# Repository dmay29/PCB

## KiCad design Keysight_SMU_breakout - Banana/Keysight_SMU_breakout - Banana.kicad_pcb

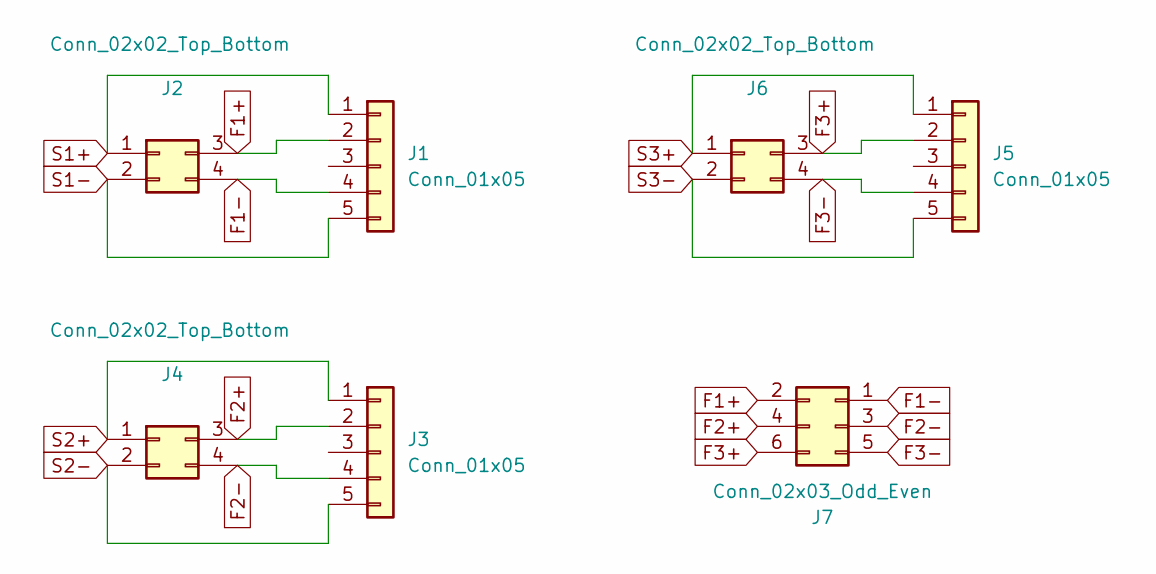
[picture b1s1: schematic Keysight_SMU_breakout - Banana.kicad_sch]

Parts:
J1, J3, J5: Conn_01x05; TerminalBlock_Phoenix_MKDS-1-5-3.81_1x05_P3.81mm_Horizontal
J2, J4, J6: Conn_02x02_Top_Bottom; Quad Banana
J7: Conn_02x03_Odd_Even; PinHeader_2x03_P2.54mm_Vertical

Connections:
F1+: J1.2, J2.3, J7.2
F1-: J1.4, J2.4, J7.1
F2+: J3.2, J4.3, J7.4
F2-: J3.4, J4.4, J7.3
F3+: J5.2, J6.3, J7.6
F3-: J5.4, J6.4, J7.5
S1+: J1.1, J2.1
S1-: J1.5, J2.2
S2+: J3.1, J4.1
S2-: J3.5, J4.2
S3+: J5.1, J6.1
S3-: J5.5, J6.2

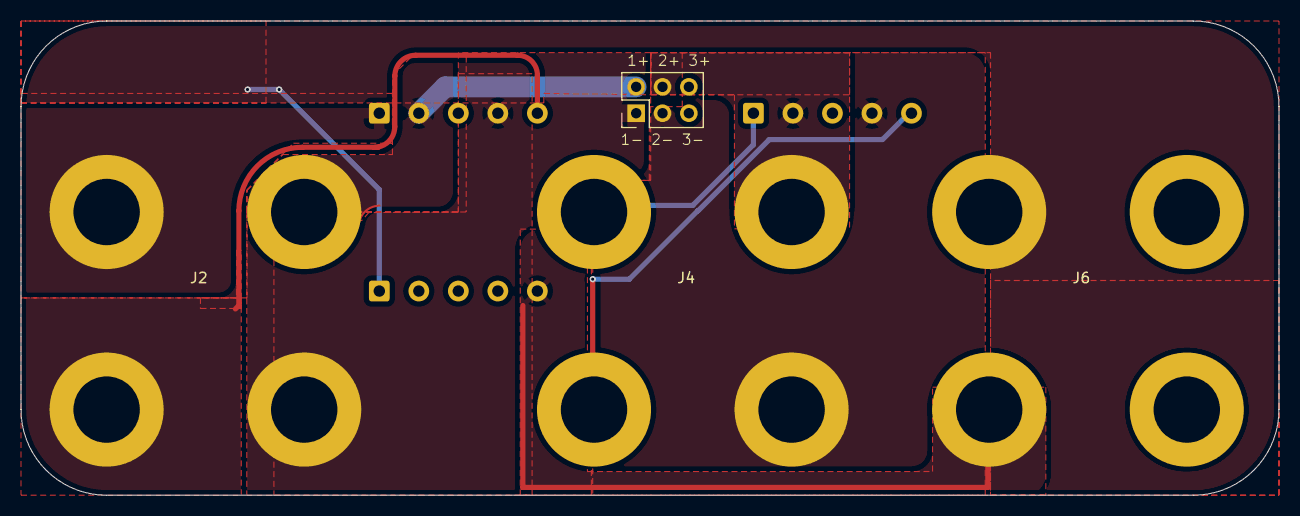
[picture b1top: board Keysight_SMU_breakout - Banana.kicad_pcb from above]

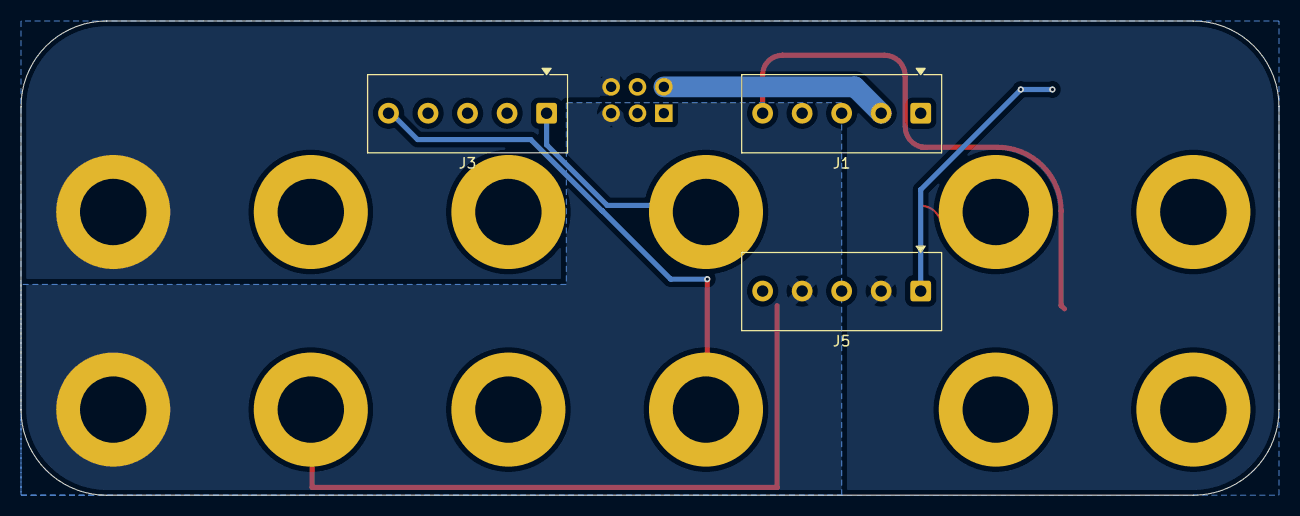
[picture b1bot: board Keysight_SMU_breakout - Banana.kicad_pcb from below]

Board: 2 copper layers, 121.3 x 45.7 mm, 7 parts (3 on the bottom side), 12 nets.

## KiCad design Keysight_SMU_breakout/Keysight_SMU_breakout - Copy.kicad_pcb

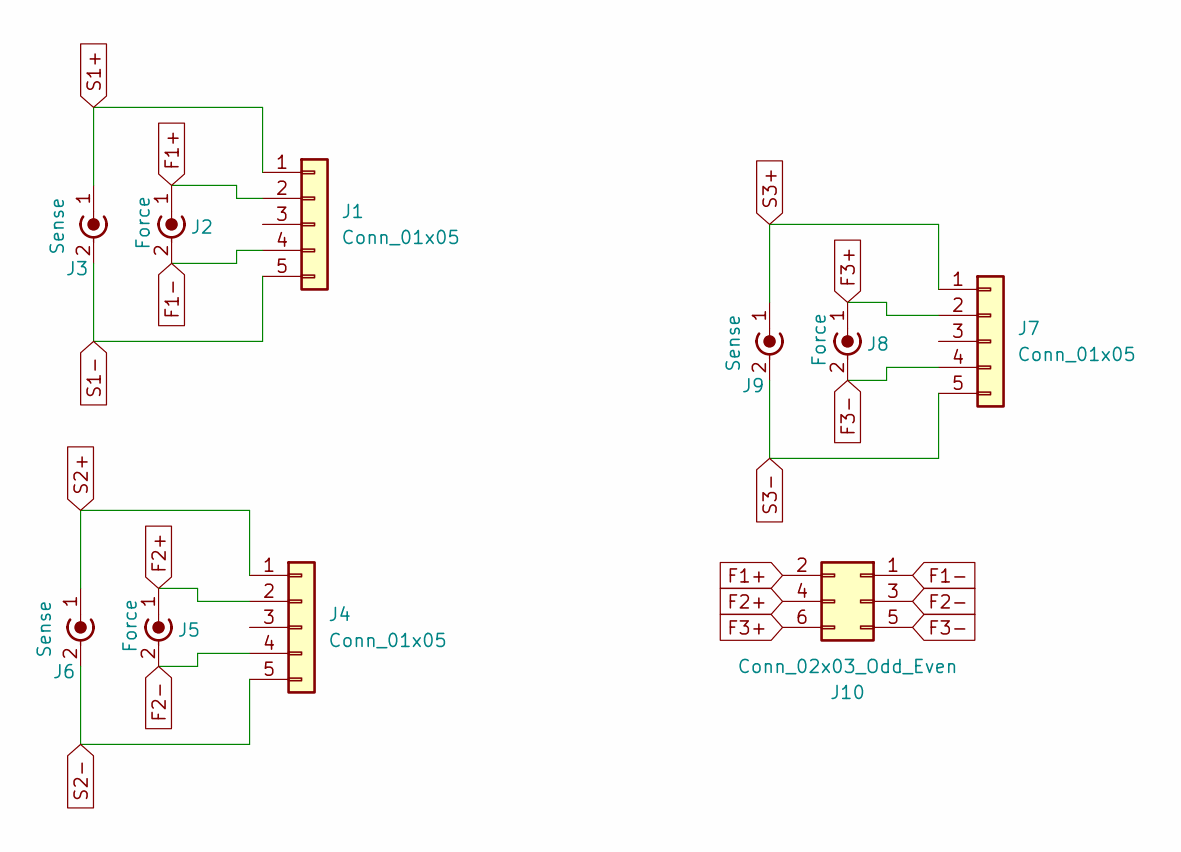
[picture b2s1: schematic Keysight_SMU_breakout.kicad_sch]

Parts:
J1, J4, J7: Conn_01x05; TerminalBlock_Phoenix_MKDS-1-5-3.81_1x05_P3.81mm_Horizontal
J2, J5, J8: Force; BNC_TEConnectivity_1478204_Vertical
J3, J6, J9: Sense; BNC_TEConnectivity_1478204_Vertical
J10: Conn_02x03_Odd_Even; PinHeader_2x03_P2.54mm_Vertical

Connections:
unnamed: J1.1, J3.1 (In)
unnamed: J1.2, J2.1 (In), J10.2
unnamed: J1.4, J2.2 (Ext), J10.1
unnamed: J1.5, J3.2 (Ext)
unnamed: J4.1, J6.1 (In)
unnamed: J4.2, J5.1 (In), J10.4
unnamed: J4.4, J5.2 (Ext), J10.3
unnamed: J4.5, J6.2 (Ext)
unnamed: J7.1, J9.1 (In)
unnamed: J7.2, J8.1 (In), J10.6
unnamed: J7.4, J8.2 (Ext), J10.5
unnamed: J7.5, J9.2 (Ext)

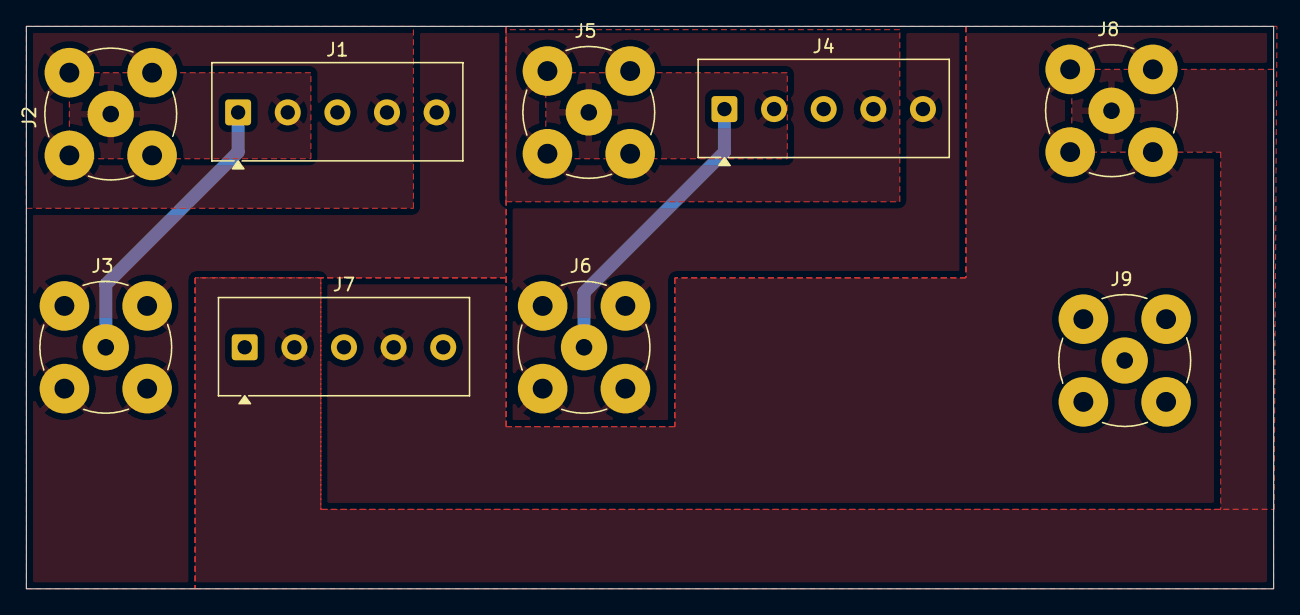
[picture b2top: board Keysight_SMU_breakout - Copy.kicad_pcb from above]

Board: 2 copper layers, 95.8 x 43.2 mm, 9 parts (0 on the bottom side), 12 nets.

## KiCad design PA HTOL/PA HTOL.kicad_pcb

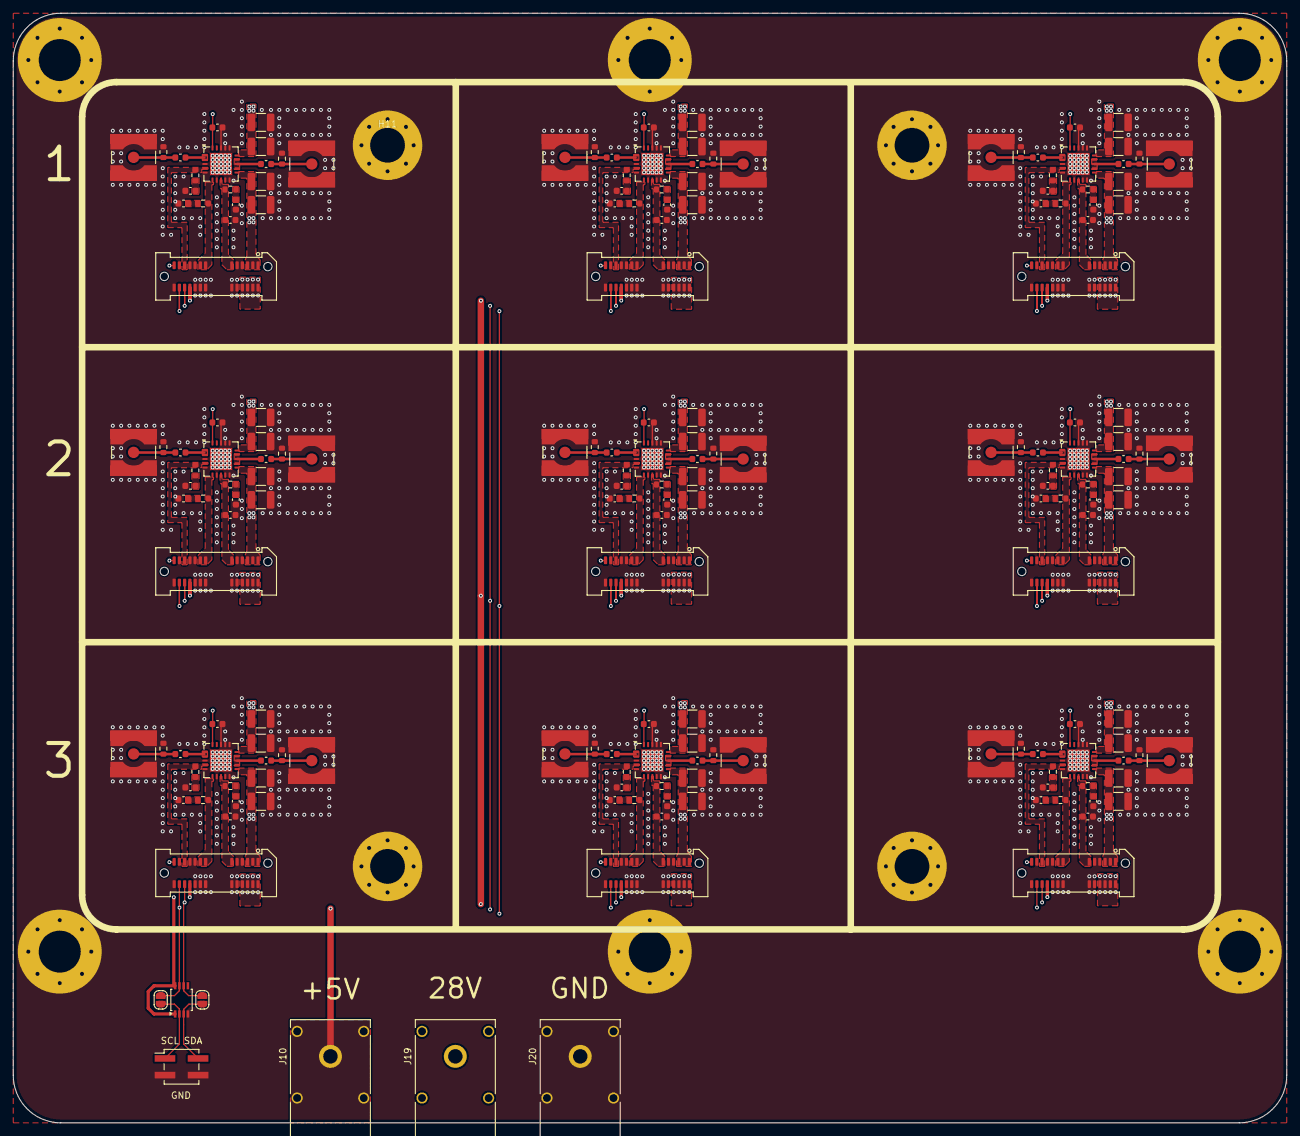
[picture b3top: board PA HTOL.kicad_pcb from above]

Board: 4 copper layers, 194.2 x 169.2 mm, 197 parts (0 on the bottom side), 115 nets.

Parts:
C1, C2, C3, C4, C5, C6, C11, C12, C13, C14, C15, C16, C17, C22, C23, C24, C25, C26, C27, C28, C33, C34, C35, C36, C37, C38, C39, C44, C45, C46, C47, C48, C49, C50, C55, C56, C57, C58, C59, C60, C61, C66, C67, C68, C69, C70, C71, C72, C77, C78, C79, C80, C81, C82, C83, C88, C89, C90, C91, C92, C93, C94, C99: C; C_0603_1608Metric
C7, C8, C9, C10, C18, C19, C20, C21, C29, C30, C31, C32, C40, C41, C42, C43, C51, C52, C53, C54, C62, C63, C64, C65, C73, C74, C75, C76, C84, C85, C86, C87, C95, C96, C97, C98: C; C_1210_3225Metric
H1, H2, H3, H4, H5, H6: MountingHole_Pad; MountingHole_6.4mm_M6_Pad_Via
H11, H12, H15, H16: MountingHole_Pad; MountingHole_5.3mm_M5_Pad_Via
J1, J2, J3, J4, J5, J6, J7, J8, J9: Conn_02x13_Odd_Even; Samtec_HSEC8-113-01-X-DV-A_2x13_P0.8mm_Pol06_Socket_Alignme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
J10, J19, J20: Conn_01x01; Banana_Cliff_FCR7350Y_S16N-PC_Horizontal shield connected
J12: Conn_02x02_Odd_Even; PinHeader_2x02_P2.54mm_Vertical_SMD
JP1, JP2: SolderJumper_2_Open; SolderJumper-2_P1.3mm_Open_RoundedPad1.0x1.5mm
R1, R2, R3, R4, R5, R6, R7, R8, R9, R10, R11, R12, R13, R14, R15, R16, R17, R18, R19, R20, R21, R22, R23, R24, R25, R26, R27, R28, R29, R30, R31, R32, R33, R34, R35, R36, R37, R38, R39, R40, R41, R42, R43, R44, R45: R; R_0603_1608Metric
RF_IN1, RF_IN2, RF_IN3, RF_IN4, RF_IN5, RF_IN6, RF_IN7, RF_IN8, RF_IN9: Conn_Coaxial; SMA_Amphenol_132134-10_Vertical
RF_OUT1, RF_OUT3, RF_OUT5, RF_OUT7, RF_OUT9, RF_OUT11, RF_OUT13, RF_OUT15, RF_OUT17: Conn_Coaxial; SMA_Amphenol_132134-10_Vertical
U1, U3, U5, U7, U9, U11, U13, U15, U17: FW8001/2; QFN-20-1EP_5x5mm_P0.65mm_EP3.35x3.35mm
U2: PCA9317; TSSOP-8_3x3mm_P0.65mm

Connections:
28V: J1.2, J1.4, J1.6, J1.8, J2.2, J2.4, J2.6, J2.8, J3.2, J3.4, J3.6, J3.8, J4.2, J4.4, J4.6, J4.8, J5.2, J5.4, J5.6, J5.8, J6.2, J6.4, J6.6, J6.8, J7.2, J7.4, J7.6, J7.8, J8.2, J8.4, J8.6, J8.8, J9.2, J9.4, J9.6, J9.8, J19.1
+5V: J1.20, J2.20, J3.20, J4.20, J5.20, J6.20, J7.20, J8.20, J9.20, J10.1, U2.1 (VDDA), U2.8 (VDDB)
/PA1/T+: C15.1, J1.25, U3.20 (T-)
/PA1/VD1: J1.13, J1.15, R8.1, U3.6 (VD1)
/PA1/VD2: C18.1, C19.2, C20.2, C21.1, J1.1, J1.3, J1.5, U3.11 (VD2), U3.15 (VD2)
/PA1/VG1: J1.21, R7.1, U3.4 (VG1)
/PA1/VG2: C16.2, J1.11, R9.1, U3.8 (VG2)
/PA2/T+: C26.1, J3.25, U5.20 (T-)
/PA2/VD1: J3.13, J3.15, R13.1, U5.6 (VD1)
/PA2/VD2: C29.1, C30.2, C31.2, C32.1, J3.1, J3.3, J3.5, U5.11 (VD2), U5.15 (VD2)
/PA2/VG1: J3.21, R12.1, U5.4 (VG1)
/PA2/VG2: C27.2, J3.11, R14.1, U5.8 (VG2)
/PA3/T+: C4.1, J2.25, U1.20 (T-)
/PA3/VD1: J2.13, J2.15, R3.1, U1.6 (VD1)
/PA3/VD2: C7.1, C8.2, C9.2, C10.1, J2.1, J2.3, J2.5, U1.11 (VD2), U1.15 (VD2)
/PA3/VG1: J2.21, R2.1, U1.4 (VG1)
/PA3/VG2: C5.2, J2.11, R4.1, U1.8 (VG2)
/PA4/T+: C37.1, J4.25, U7.20 (T-)
/PA4/VD1: J4.13, J4.15, R18.1, U7.6 (VD1)
/PA4/VD2: C40.1, C41.2, C42.2, C43.1, J4.1, J4.3, J4.5, U7.11 (VD2), U7.15 (VD2)
/PA4/VG1: J4.21, R17.1, U7.4 (VG1)
/PA4/VG2: C38.2, J4.11, R19.1, U7.8 (VG2)
/PA5/T+: C59.1, J5.25, U11.20 (T-)
/PA5/VD1: J5.13, J5.15, R28.1, U11.6 (VD1)
/PA5/VD2: C62.1, C63.2, C64.2, C65.1, J5.1, J5.3, J5.5, U11.11 (VD2), U11.15 (VD2)
/PA5/VG1: J5.21, R27.1, U11.4 (VG1)
/PA5/VG2: C60.2, J5.11, R29.1, U11.8 (VG2)
/PA6/T+: C48.1, J6.25, U9.20 (T-)
/PA6/VD1: J6.13, J6.15, R23.1, U9.6 (VD1)
/PA6/VD2: C51.1, C52.2, C53.2, C54.1, J6.1, J6.3, J6.5, U9.11 (VD2), U9.15 (VD2)
/PA6/VG1: J6.21, R22.1, U9.4 (VG1)
/PA6/VG2: C49.2, J6.11, R24.1, U9.8 (VG2)
/PA7/T+: C70.1, J7.25, U13.20 (T-)
/PA7/VD1: J7.13, J7.15, R33.1, U13.6 (VD1)
/PA7/VD2: C73.1, C74.2, C75.2, C76.1, J7.1, J7.3, J7.5, U13.11 (VD2), U13.15 (VD2)
/PA7/VG1: J7.21, R32.1, U13.4 (VG1)
/PA7/VG2: C71.2, J7.11, R34.1, U13.8 (VG2)
/PA8/T+: C92.1, J8.25, U17.20 (T-)
/PA8/VD1: J8.13, J8.15, R43.1, U17.6 (VD1)
/PA8/VD2: C95.1, C96.2, C97.2, C98.1, J8.1, J8.3, J8.5, U17.11 (VD2), U17.15 (VD2)
/PA8/VG1: J8.21, R42.1, U17.4 (VG1)
/PA8/VG2: C93.2, J8.11, R44.1, U17.8 (VG2)
/PA9/T+: C81.1, J9.25, U15.20 (T-)
/PA9/VD1: J9.13, J9.15, R38.1, U15.6 (VD1)
/PA9/VD2: C84.1, C85.2, C86.2, C87.1, J9.1, J9.3, J9.5, U15.11 (VD2), U15.15 (VD2)
/PA9/VG1: J9.21, R37.1, U15.4 (VG1)
/PA9/VG2: C82.2, J9.11, R39.1, U15.8 (VG2)
GND: C2.1, C3.1, C4.2, C5.1, C6.1, C7.2, C8.1, C9.1, C10.2, C13.1, C14.1, C15.2, C16.1, C17.1, C18.2, C19.1, C20.1, C21.2, C24.1, C25.1, C26.2, C27.1, C28.1, C29.2, C30.1, C31.1, C32.2, C35.1, C36.1, C37.2, C38.1, C39.1, C40.2, C41.1, C42.1, C43.2, C46.1, C47.1, C48.2, C49.1, C50.1, C51.2, C52.1, C53.1, C54.2, C57.1, C58.1, C59.2, C60.1, C61.1, C62.2, C63.1, C64.1, C65.2, C68.1, C69.1, C70.2, C71.1, C72.1, C73.2, C74.1, C75.1, C76.2, C79.1, C80.1, C81.2, C82.1, C83.1, C84.2, C85.1, C86.1, C87.2, C90.1, C91.1, C92.2, C93.1, C94.1, C95.2, C96.1, C97.1, C98.2, H1.1, H2.1, H3.1, H4.1, H5.1, H6.1, H11.1, H12.1, H15.1, H16.1, J1.7, J1.9, J1.10, J1.12, J1.14, J1.16, J1.17, J1.18, J1.19, J1.23, J1.26, J2.7, J2.9, J2.10, J2.12, J2.14, J2.16, J2.17, J2.18, J2.19, J2.23, J2.26, J3.7, J3.9, J3.10, J3.12, J3.14, J3.16, J3.17, J3.18, J3.19, J3.23, J3.26, J4.7, J4.9, J4.10, J4.12, J4.14, J4.16, J4.17, J4.18, J4.19, J4.23, J4.26, J5.7, J5.9, J5.10, J5.12, J5.14, J5.16, J5.17, J5.18, J5.19, J5.23, J5.26, J6.7, J6.9, J6.10, J6.12, J6.14, J6.16, J6.17, J6.18, J6.19, J6.23, J6.26, J7.7, J7.9, J7.10, J7.12, J7.14, J7.16, J7.17, J7.18, J7.19, J7.23, J7.26, J8.7, J8.9, J8.10, J8.12, J8.14, J8.16, J8.17, J8.18, J8.19, J8.23, J8.26, J9.7, J9.9, J9.10, J9.12, J9.14, J9.16, J9.17, J9.18, J9.19, J9.23, J9.26, J12.3, J12.4, J20.1, R1.2, R5.2, R6.2, R10.2, R11.2, R15.2, R16.2, R20.2, R21.2, R25.2, R26.2, R30.2, R31.2, R35.2, R36.2, R40.2, R41.2, R45.2, RF_IN1.2 (Ext), RF_IN2.2 (Ext), RF_IN3.2 (Ext), RF_IN4.2 (Ext), RF_IN5.2 (Ext), RF_IN6.2 (Ext), RF_IN7.2 (Ext), RF_IN8.2 (Ext), RF_IN9.2 (Ext), RF_OUT1.2 (Ext), RF_OUT3.2 (Ext), RF_OUT5.2 (Ext), RF_OUT7.2 (Ext), RF_OUT9.2 (Ext), RF_OUT11.2 (Ext), RF_OUT13.2 (Ext), RF_OUT15.2 (Ext), RF_OUT17.2 (Ext), U1.3 (GND), U1.5 (GND), U1.7 (GND), U1.9 (GND), U1.10 (GND), U1.16 (GND), U1.17 (GND), U1.18 (T+), U1.21 (PAD_GND), U2.4 (GND), U3.3 (GND), U3.5 (GND), U3.7 (GND), U3.9 (GND), U3.10 (GND), U3.16 (GND), U3.17 (GND), U3.18 (T+), U3.21 (PAD_GND), U5.3 (GND), U5.5 (GND), U5.7 (GND), U5.9 (GND), U5.10 (GND), U5.16 (GND), U5.17 (GND), U5.18 (T+), U5.21 (PAD_GND), U7.3 (GND), U7.5 (GND), U7.7 (GND), U7.9 (GND), U7.10 (GND), U7.16 (GND), U7.17 (GND), U7.18 (T+), U7.21 (PAD_GND), U9.3 (GND), U9.5 (GND), U9.7 (GND), U9.9 (GND), U9.10 (GND), U9.16 (GND), U9.17 (GND), U9.18 (T+), U9.21 (PAD_GND), U11.3 (GND), U11.5 (GND), U11.7 (GND), U11.9 (GND), U11.10 (GND), U11.16 (GND), U11.17 (GND), U11.18 (T+), U11.21 (PAD_GND), U13.3 (GND), U13.5 (GND), U13.7 (GND), U13.9 (GND), U13.10 (GND), U13.16 (GND), U13.17 (GND), U13.18 (T+), U13.21 (PAD_GND), U15.3 (GND), U15.5 (GND), U15.7 (GND), U15.9 (GND), U15.10 (GND), U15.16 (GND), U15.17 (GND), U15.18 (T+), U15.21 (PAD_GND), U17.3 (GND), U17.5 (GND), U17.7 (GND), U17.9 (GND), U17.10 (GND), U17.16 (GND), U17.17 (GND), U17.18 (T+), U17.21 (PAD_GND)
unnamed: C1.2, U1.1 (RF_IN), U1.2 (RF_IN)
unnamed: C2.2, R2.2
unnamed: C3.2, R3.2
unnamed: C6.2, R4.2
unnamed: C11.2, U1.12 (RF_OUT), U1.13 (RF_OUT), U1.14 (RF_OUT)
unnamed: C12.2, U3.1 (RF_IN), U3.2 (RF_IN)
unnamed: C13.2, R7.2
unnamed: C14.2, R8.2
unnamed: C17.2, R9.2
unnamed: C22.2, U3.12 (RF_OUT), U3.13 (RF_OUT), U3.14 (RF_OUT)
unnamed: C23.2, U5.1 (RF_IN), U5.2 (RF_IN)
unnamed: C24.2, R12.2
unnamed: C25.2, R13.2
unnamed: C28.2, R14.2
unnamed: C33.2, U5.12 (RF_OUT), U5.13 (RF_OUT), U5.14 (RF_OUT)
unnamed: C34.2, U7.1 (RF_IN), U7.2 (RF_IN)
unnamed: C35.2, R17.2
unnamed: C36.2, R18.2
unnamed: C39.2, R19.2
unnamed: C44.2, U7.12 (RF_OUT), U7.13 (RF_OUT), U7.14 (RF_OUT)
unnamed: C45.2, U9.1 (RF_IN), U9.2 (RF_IN)
unnamed: C46.2, R22.2
unnamed: C47.2, R23.2
unnamed: C50.2, R24.2
unnamed: C55.2, U9.12 (RF_OUT), U9.13 (RF_OUT), U9.14 (RF_OUT)
unnamed: C56.2, U11.1 (RF_IN), U11.2 (RF_IN)
unnamed: C57.2, R27.2
unnamed: C58.2, R28.2
unnamed: C61.2, R29.2
unnamed: C66.2, U11.12 (RF_OUT), U11.13 (RF_OUT), U11.14 (RF_OUT)
unnamed: C67.2, U13.1 (RF_IN), U13.2 (RF_IN)
unnamed: C68.2, R32.2
unnamed: C69.2, R33.2
unnamed: C72.2, R34.2
unnamed: C77.2, U13.12 (RF_OUT), U13.13 (RF_OUT), U13.14 (RF_OUT)
unnamed: C78.2, U15.1 (RF_IN), U15.2 (RF_IN)
unnamed: C79.2, R37.2
unnamed: C80.2, R38.2
unnamed: C83.2, R39.2
unnamed: C88.2, U15.12 (RF_OUT), U15.13 (RF_OUT), U15.14 (RF_OUT)
unnamed: C89.2, U17.1 (RF_IN), U17.2 (RF_IN)
unnamed: C90.2, R42.2
unnamed: C91.2, R43.2
unnamed: C94.2, R44.2
unnamed: C99.2, U17.12 (RF_OUT), U17.13 (RF_OUT), U17.14 (RF_OUT)
unnamed: C1.1, R1.1, RF_IN1.1 (In)
unnamed: C12.1, R6.1, RF_IN2.1 (In)
unnamed: C23.1, R11.1, RF_IN3.1 (In)
unnamed: C34.1, R16.1, RF_IN4.1 (In)
unnamed: C45.1, R21.1, RF_IN5.1 (In)
unnamed: C56.1, R26.1, RF_IN6.1 (In)
unnamed: C67.1, R31.1, RF_IN7.1 (In)
unnamed: C78.1, R36.1, RF_IN8.1 (In)
unnamed: C89.1, R41.1, RF_IN9.1 (In)
unnamed: C11.1, R5.1, RF_OUT1.1 (In)
unnamed: C22.1, R10.1, RF_OUT3.1 (In)
unnamed: C33.1, R15.1, RF_OUT5.1 (In)
unnamed: C44.1, R20.1, RF_OUT7.1 (In)
unnamed: C55.1, R25.1, RF_OUT9.1 (In)
unnamed: C66.1, R30.1, RF_OUT11.1 (In)
unnamed: C77.1, R35.1, RF_OUT13.1 (In)
unnamed: C88.1, R40.1, RF_OUT15.1 (In)
unnamed: C99.1, R45.1, RF_OUT17.1 (In)
SCL: J1.24, J2.24, J3.24, J4.24, J5.24, J6.24, J7.24, J8.24, J9.24, JP1.2 (B), U2.7 (SCLB)
SCL_ext: J12.1, JP1.1 (A), U2.2 (SCLA)
SDA: J1.22, J2.22, J3.22, J4.22, J5.22, J6.22, J7.22, J8.22, J9.22, JP2.2 (B), U2.6 (SDAB)
SDA_ext: J12.2, JP2.1 (A), U2.3 (SDAA)

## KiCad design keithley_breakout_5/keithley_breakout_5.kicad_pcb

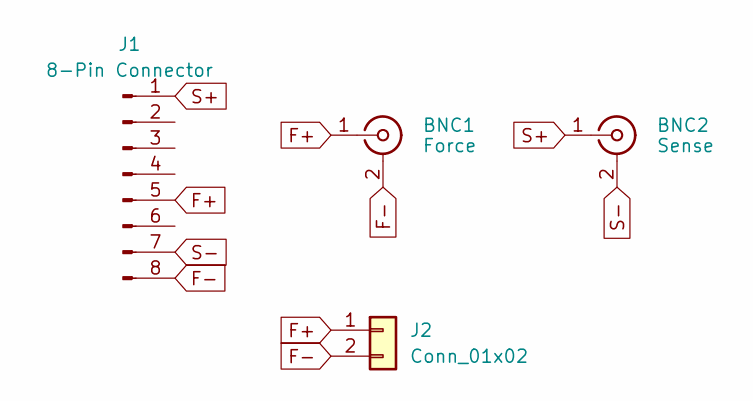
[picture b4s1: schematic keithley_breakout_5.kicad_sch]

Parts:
BNC1: Force; BNC_TEConnectivity_1478204_Vertical
BNC2: Sense; BNC_TEConnectivity_1478204_Vertical
J1: 8-Pin Connector; PhoenixContact_MSTBV_2,5_8-GF-5,08_1x08_P5.08mm_Vertical_Th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
J2: Conn_01x02; Dual Banana

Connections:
F+: BNC1.1 (In), J1.5, J2.1
F-: BNC1.2 (Ext), J1.8, J2.2
S+: BNC2.1 (In), J1.1
S-: BNC2.2 (Ext), J1.7

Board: 2 copper layers, 4 parts (1 on the bottom side), 4 nets, no tracks yet.
